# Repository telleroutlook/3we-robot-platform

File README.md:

<div align="center">

# 3WE Robot Platform

**AI-First Open Infrastructure for Embodied Robotics**

[-orange.svg)](sdk/threewe/)

An open-source robot platform for Embodied AI research — a consistent Python API
across simulation and real hardware, with <$500 reproducible hardware.

> **Status:** Active development. Mock backend is functional. Hardware builds and Gazebo integration are being validated — no completed physical prototype video yet.

> **A note on Sim2Real:** The Python API stays the same when you switch backends, but
> sim-to-real transfer in practice still requires task-specific tuning (sensor models,
> noise, dynamics). We provide presets for common scenarios; we don't claim the gap
> away. See [Sim-to-Real Gap](docs/sim_to_real_gap.md) for what works, what doesn't,
> and where you'll likely need to do downstream work.

*Autonomous navigation in office_v2 scene — 360° LiDAR, real-time obstacle avoidance, 4 lines of Python*

</div>

> **Note:** The animation above is a concept demo (generated with matplotlib), not a Gazebo simulation or real hardware recording. It illustrates the target API and navigation behavior.

### Try it now — 30 seconds, zero dependencies beyond numpy

<div align="center">

</div>

```bash
git clone https://github.com/telleroutlook/3we-robot-platform.git
cd 3we-robot-platform && pip install -e sdk/threewe/
python examples/navigate_office.py
```

> The recording was made with [`demo/record_demo.sh`](demo/record_demo.sh) — clone the repo and run it yourself to verify.

---

## 5 Lines to a Moving Robot

```python
from threewe import Robot

async with Robot(backend="mock") as robot:
    image = robot.get_image()
    await robot.move_to(x=2.0, y=1.0)
    pose = robot.get_pose()
```

Switch `backend="mock"` to `backend="gazebo"` or `backend="real"` — the Python API stays the same. Sensor models and sim configs may still need task-specific tuning; see [Sim-to-Real Gap](docs/sim_to_real_gap.md).

---

## Why 3we?

| If you are... | 3we gives you... | Start here |
|:---|:---|:---|
| **AI/ML Researcher** | Gymnasium envs, VLM/VLA integration, trajectory recording — focus on your model, not ROS2 | [Getting Started (AI)](docs/getting_started_ai.md) |
| **Robotics Student** | Full stack from PCB to Python, <$500 hardware, production-grade code instead of toy examples | [Getting Started (Basic)](docs/getting_started_basic.md) |
| **RL Practitioner** | `gymnasium.make("3we/Navigation-v1")` — standard RL interface with sim-to-real presets for common tasks | [Getting Started (AI)](docs/getting_started_ai.md) |
| **Hardware Builder** | Open BOM, assembly guide, CERN-OHL-P licensed PCB + structure | [Assembly Guide](docs/assembly_guide.md) |

---

## Quick Start

> **Status:** The `threewe` SDK is under active development. `pip install threewe` is not yet available on PyPI. Install from source to try it today:

```bash
git clone https://github.com/telleroutlook/3we-robot-platform.git
cd 3we-robot-platform
pip install -e sdk/threewe/
```

```python
import asyncio
from threewe import Robot

async def main():
    # "mock" backend works immediately — no ROS2 or Gazebo required
    async with Robot(backend="mock") as robot:
        # Navigate
        result = await robot.move_to(x=2.0, y=1.0)
        print(f"Reached: {result.success}")

        # VLM-powered instruction (requires: pip install threewe[ai])
        result = await robot.execute_instruction("go to the red door")

        # Get sensor data
        scan = robot.get_lidar_scan()
        imu = robot.get_imu()

asyncio.run(main())
```

> **Backends**: Use `backend="mock"` to try the API instantly, `"gazebo"` for physics simulation (requires ROS2), `"isaac_sim"` for GPU-accelerated parallel simulation, or `"real"` for physical hardware.

<details>
<summary><b>Actual output (from the recording above)</b></summary>

```console
$ pip install -e sdk/threewe/
Successfully installed threewe-0.1.0a0

$ python examples/navigate_office.py
============================================================
  3we Robot Platform — Office Navigation Demo
============================================================

[3we] Robot initialized  backend=mock  scene=office_v2

  Start pose: (1.0, 1.0)
  LiDAR: 360 rays, nearest obstacle: 0.99m

  Following path: 5 waypoints

[3we] Navigating to (2.0, 3.0)...
[3we] Planning path... distance=2.2m
[3we]   pos=(1.5, 2.1)  heading=63°  remaining=1.0m
[3we] Goal reached  distance=2.2m  time=4.5s
[3we] Navigating to (7.0, 3.5)...
[3we] Planning path... distance=5.0m
[3we]   pos=(4.0, 3.2)  heading=6°  remaining=3.0m
[3we] Goal reached  distance=5.0m  time=10.0s
...

  Final pose: (12.0, 10.0)
  Total distance: 20.5m
  Result: success

============================================================
```

</details>

### RL Training

```python
import gymnasium
import threewe.gym  # registers environments

env = gymnasium.make("3we/Navigation-v1")
obs, info = env.reset()

for _ in range(1000):
    action = env.action_space.sample()
    obs, reward, terminated, truncated, info = env.step(action)
    if terminated or truncated:
        obs, info = env.reset()
```

### Benchmarks

```bash
threewe benchmark run --task pointnav --episodes 100 --backend gazebo
```

See the [Benchmark Leaderboard](docs/leaderboard.md) for baseline results and submission instructions.

---

## Capabilities

| Capability | Status | Details |
|------------|--------|---------|
| Consistent Python API across backends | ✅ Ready | 4 backends (mock/gazebo/isaac_sim/real), same Robot class — task-specific sim tuning still required ([details](docs/sim_to_real_gap.md)) |
| Imitation Learning Data | ✅ Ready | `save_lerobot()` export + HuggingFace Hub push/pull |
| VLM/LLM Control | ✅ Ready | GPT-4o / Qwen-VL, async API decoupled from 50Hz control loop |
| Hardware Safety | ✅ Ready | 3-tier watchdog: 500ms cmd_vel timeout, 1s software WDT, 1.6s hardware WDT (TPS3813) |
| RL Gymnasium Envs | ✅ Ready | 4 standard envs (PointNav, Exploration, ObjectNav, VLN) + multi-agent |
| Edge AI Inference | ✅ Ready | Hailo-8L M.2 accelerator (13 TOPS) on Raspberry Pi 5 |
| VLA Model Deploy | ✅ Ready | ONNX / PyTorch / Hailo HEF, `from_pretrained()` from Hub |
| Domain Randomization | ✅ Ready | Physics, visual, and sensor noise — configurable per-episode |
| RGB-D Depth Camera | ✅ Ready | `get_rgbd_image()` API, native depth in Isaac Sim |
| Modular Install | ✅ Ready | `threewe` / `threewe[sim]` / `threewe[ai]` / `threewe[all]` |

---

## Architecture

```mermaid
flowchart TB
    A["<b>Your Python Code</b><br/>robot.move_to() · robot.get_image() · robot.execute_instruction()"]
    B["<b>threewe Python API</b><br/>Robot · Types · Config · AI (VLM/VLA) · Gym · Data · Benchmark"]
    C1["<b>MockBackend</b><br/>Zero-dep 2D<br/>kinematic sim"]
    C2["<b>GazeboBackend</b><br/>Gazebo Harmonic<br/>+ ros_gz_bridge"]
    C3["<b>RealBackend</b><br/>ROS2 Topics"]
    C4["<b>IsaacSimBackend</b><br/>GPU-accelerated<br/>parallel RL"]
    D["<b>ROS2 Jazzy + Nav2</b><br/>/cmd_vel · /scan · /odom · /camera · NavigateToPose Action"]
    E["<b>Firmware (ESP32-S3)</b><br/>Motor PID · Encoders · IMU · Safety Relay · micro-ROS"]
    F["<b>Hardware Layer</b><br/>Mecanum · DRV8833 · HC-SR04/LD06 · BNO055 · Battery · E-Stop"]

    A --> B
    B --> C1 & C2 & C3 & C4
    C1 & C2 & C3 & C4 --> D
    D --> E
    E --> F
```

---

## Platform Comparison

> Different tools for different needs. This table highlights where 3we fits — it is not a claim of superiority.

| Feature | **3we** | TurtleBot 4 | LeRobot | Isaac Lab |
|:--------|:---:|:---:|:---:|:---:|
| Python API (no ROS2 knowledge needed) | Yes | No | N/A | Partial |
| Same API, mock → sim → real | Yes | No | No | Yes |
| Open Hardware (PCB + BOM) | Full | Partial | N/A | N/A |
| Gymnasium Interface | Yes | No | Partial | Yes |
| VLM/VLA Integration | Yes | No | Yes | No |
| Hardware Cost | <$500 | ~$1200 | ~$2000+ | N/A |
| Payload Hot-plug Bus | PBC-34 | USB | N/A | N/A |
| Safety (HW E-stop) | Yes | Software | N/A | N/A |
| Community / Maturity | Early stage | Established | Active | Active |

---

## Hardware Specs

| Spec | Standard v2 |
|:-----|:---|
| Drive | 4-wheel Mecanum (65mm), omnidirectional |
| MCU | ESP32-S3 (dual-core 240MHz) |
| SBC | Raspberry Pi 5 (8GB) |
| AI Accelerator | Hailo-8L (13 TOPS) |
| LiDAR | LD06 (360°, 12m range) |
| IMU | BNO055 (9-axis fused) |
| Max Velocity | 0.5 m/s linear, 1.0 rad/s angular |
| Battery | 7.4V Li-ion, ~2h runtime |
| Safety | ISO 13850-inspired hardware E-stop + dual-channel relay (not certified) |
| Connectivity | Wi-Fi + BLE (+ 4G/5G optional) |
| Reproduction Cost | <$500 |

---

## Repository Structure

```
3we-robot-platform/
├── sdk/threewe/          # AI-First Python package (pip install threewe)
│   ├── src/threewe/      #   Robot, Types, Backends, Gym, AI, Data, Benchmark
│   └── tests/            #   309 unit tests
├── examples/             # Ready-to-run demo scripts
├── firmware/             # ESP32-S3 firmware (ESP-IDF + micro-ROS)
├── ros2_ws/              # ROS2 packages (Nav2, SLAM, Gazebo, Perception)
├── hardware/             # Open hardware (KiCad PCB, BOM, mechanical)
├── sdk/payload_interface/# Payload communication library
├── sdk/web_control/      # TypeScript Web Components control panel
├── monitoring/           # Prometheus + Grafana observability
└── docs/                 # Guides, API reference, tutorials
```

---

## Installation Options

> **Current**: Install from source with `pip install -e sdk/threewe/`. The commands below will work once the package is published to PyPI.

```bash
# Core (types, Robot class, config)
pip install threewe

# With simulation (adds gymnasium)
pip install threewe[sim]

# With AI integration (adds openai, Pillow)
pip install threewe[ai]

# With data recording (adds h5py)
pip install threewe[data]

# Everything
pip install threewe[all]
```

For the **real hardware** backend, you also need ROS2 Jazzy:
```bash
# Ubuntu 24.04
sudo apt install ros-jazzy-desktop
```

---

## Examples

| Script | Description | Backend |
|:-------|:-----------|:--------|
| [`navigate_office.py`](examples/navigate_office.py) | Multi-waypoint navigation with verbose output | mock |
| [`hello_world.py`](examples/hello_world.py) | Connect, capture image, navigate | mock |
| [`rl_obstacle_avoidance.py`](examples/rl_obstacle_avoidance.py) | PPO training in simulation | mock |
| [`slam_exploration.py`](examples/slam_exploration.py) | Autonomous SLAM exploration | mock |
| [`data_collection.py`](examples/data_collection.py) | Record trajectories for imitation learning | mock |
| [`vlm_navigation.py`](examples/vlm_navigation.py) | GPT-4o visual navigation | mock + API key |
| [`sim2real_demo.py`](examples/sim2real_demo.py) | Same code, different backends | gazebo |

### Jupyter Notebooks

Step-by-step tutorials in [`notebooks/`](notebooks/). Most require ROS2 + Gazebo unless noted:

| Notebook | Topic | Requires |
|:---------|:------|:---------|
| [01_hello_world](notebooks/01_hello_world.ipynb) | Connect, sensors, basic navigation | Gazebo |
| [02_slam_exploration](notebooks/02_slam_exploration.ipynb) | Autonomous mapping | Gazebo |
| [03_point_navigation](notebooks/03_point_navigation.ipynb) | Waypoints and path following | Gazebo |
| [04_rl_training](notebooks/04_rl_training.ipynb) | Gymnasium + PPO training | mock (works standalone) |
| [05_data_collection](notebooks/05_data_collection.ipynb) | Record trajectories, export to LeRobot | Gazebo |

---

## Roadmap

- [x] **Phase 1**: ESP32 firmware + ROS2 stack + Hardware design
- [x] **Phase 1**: `threewe` Python API + Mock backend
- [x] **Phase 1**: Gymnasium environments + VLM/VLA integration
- [x] **Phase 1**: Benchmark framework + Example scripts
- [ ] **Phase 1**: Gazebo/Isaac Sim backends (interface done, integration testing in progress)
- [ ] **Phase 1**: PyPI publishing (`pip install threewe`)
- [x] **Phase 2**: On-robot status display panel (1.3" OLED SH1106, 3-key navigation, 5 pages, fault codes)
- [ ] **Phase 2**: Hardware Abstraction Layer for 3rd-party robots
- [ ] **Phase 2**: Foundation model fine-tuning pipelines
- [ ] **Phase 3**: 3we Hub (model/dataset sharing)
- [ ] **Phase 3**: Multi-robot fleet management

---

## Blog & Dev Notes

Engineering deep-dives at [3we.org/blog](https://3we.org/blog/overview/):

| Post | Topic |
|:-----|:------|
| [Dev Log #1: Why These Parts](https://3we.org/blog/dev-log-001/) | ESP32-S3 vs STM32, mecanum wheels, PBC-34 bus design, honest project status |
| [Sim2Real: Same Code to Real Hardware](https://3we.org/blog/sim2real-practice/) | Backend abstraction, domain randomization, validation protocol |
| [Build a $300 ROS2 Research Robot](https://3we.org/blog/build-robot/) | Complete BOM, assembly, software setup |
| [30 Lines: Let GPT-4o Control a Robot](https://3we.org/blog/vlm-control/) | VLM perception-action loop, local model support |

---

## Licensing

| Component | License | File |
|:----------|:--------|:-----|
| Firmware & Software | Apache License 2.0 | [`LICENSE`](LICENSE) |
| Hardware Designs | CERN-OHL-P v2 | [`LICENSE-HARDWARE`](LICENSE-HARDWARE) |
| Documentation | CC BY-SA 4.0 | [`LICENSE-DOCS`](LICENSE-DOCS) |

### Attribution

Commercial use is welcome and free of charge. The licenses require that derivative
works include attribution to this project. Recommended format:

> This product is based on the open-source [3we Robot Platform](https://github.com/telleroutlook/3we-robot-platform).

For academic citations, see [`CITATION.cff`](CITATION.cff).

---

## Contributing

We welcome contributions! See **[CONTRIBUTING.md](CONTRIBUTING.md)** for development setup, branch strategy, and PR process.

---

## Safety Notice

> [!WARNING]
> This platform contains **moving mechanical parts** and **lithium batteries**.

- Safety relay design is **inspired by** ISO 13850 but is **not certified** — do not use for safety-critical applications without independent certification
- Always verify E-stop function before operation
- Never bypass or modify the safety relay circuit
- Follow battery handling guidelines in documentation

---

<div align="center">

Copyright 2025-2026 [telleroutlook](https://github.com/telleroutlook) · [3we-robot-platform](https://github.com/telleroutlook/3we-robot-platform)

</div>

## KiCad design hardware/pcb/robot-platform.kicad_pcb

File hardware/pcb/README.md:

# PCB Design Documentation

## Overview

The robot-platform mainboard integrates the ESP32-S3 MCU, motor drivers, power management, sensor interfaces, and the PBC-34 payload connector on a single 4-layer PCB.

## Board Specifications

| Parameter | Value |
|-----------|-------|
| Dimensions | 120 × 90 mm |
| Layers | 4 (Signal - GND - Power - Signal) |
| Minimum trace width | 0.15 mm |
| Minimum via | 0.3 mm drill / 0.6 mm pad |
| Clearance | 0.2 mm |
| Copper weight | 1 oz (outer), 1 oz (inner) |
| Surface finish | ENIG (lead-free) |
| Board thickness | 1.6 mm |

## Layer Stack

| Layer | Usage |
|-------|-------|
| Top | Signal traces, component pads |
| Inner 1 | Ground plane (unbroken) |
| Inner 2 | Power distribution (VBAT, 5V, 3.3V, 12V) |
| Bottom | Signal traces, component pads |

## Power Architecture

```
Battery Pack(s) ─── XT30 ──→ Q8 P-MOS ──→ VBAT Bus (7.4V)
                              (reverse      │
                              protection)   │
                    ┌──────────────────────────┼──────────────────────┐
                    │                          │                      │
                    ▼                          ▼                      ▼
              MP2359 Buck              MP1584EN Buck            [Safety Relay]
              5V / 1.2A                5V / 5A                       │
              (ESP32, sensors)              │                    Coil supply:
                    │               ┌──────┼──────┐           +5V_ESP → SW1b NC
                    ▼               │      │      │           → +5V_ESTOP_COIL
              AP2112K-3.3        Q6a/Q6b   Q3                 → RLY1 coil
              3.3V / 600mA       P-MOS SW  P-MOS SW                  │
              (logic, I2C)          │         │                      ▼
                                    ▼         ▼               Motor DRV8833
                              +5V_PI_SW   +5V_PAYLOAD         (7.4V / 10A max)
                              (Pi5, 3A)   (Payload, 2A)
                              GPIO45 ctrl  MCP23017 ctrl
```

### Supervisory Circuits

- **TPS3813 (U10)**: External watchdog, 1.6s timeout. GPIO46 toggles WDI; if firmware
  hangs, RST pulls ESP32 EN low → hardware reset. Independent of software watchdog.
- **Pi5 Power Switch (Q6a/Q6b/Q7)**: Dual Si2301CDS P-MOS (parallel, 5A total) with
  AO3400A N-MOS driver. GPIO45 HIGH = Pi5 ON. Default OFF at boot (R34 pull-down).
  Standard/Industrial SKU only (DNP on Basic).
- **E-stop Safety Path (SW1b → RLY1)**: The E-stop button has dual NC contact pairs.
  NC2 (SW1b) is in series with the safety relay coil +5V supply. Pressing E-stop
  physically breaks the coil circuit → relay de-energizes → motor power cut. This is
  a pure hardware interlock — zero firmware dependency, compliant with ISO 13850.
  R17 (Q5 gate pull-up) also connects to +5V_ESTOP_COIL so the N-MOS driver loses
  gate drive simultaneously.

## PBC-34 Payload Bus Connector

2×17 pin header (2.54mm pitch), keyed with polarization notch.

| Pin | Function | Rating | Notes |
|-----|----------|--------|-------|
| 1-2 | +5V Power | 3A max | P-MOS soft-start, switched from +5V_PI (MP1584EN 5A rail) via MCP23017 GPA0 |
| 3-4 | +12V Power | 3A max | MOSFET soft-start |
| 5-6 | GND (Power) | — | Wide traces (1mm) |
| 7 | I2C SDA | 3.3V | Direct (shared bus with IMU, INA219, MCP23017) |
| 8 | I2C SCL | 3.3V | Direct (shared bus with IMU, INA219, MCP23017) |
| 9 | UART TX | 3.3V | From payload to platform |
| 10 | UART RX | 3.3V | From platform to payload |
| 11-18 | GPIO ×8 | 3.3V | Via MCP23017 expander |
| 19 | USB D+ | — | Hub downstream port |
| 20 | USB D- | — | Hub downstream port |
| 21 | CAN-H | — | Industrial SKU only |
| 22 | CAN-L | — | Industrial SKU only |
| 23-24 | VBAT Direct | 10A | PPTC protected |
| 25 | ENABLE | Active low | Power control |
| 26 | FAULT | Open drain | Payload fault |
| 27 | DETECT | Mechanical | Spring contact |
| 28 | INT | Active low | Interrupt request |
| 29 | +3.3V Ref | 100mA | Logic reference |
| 30 | ID SCL | — | EEPROM discovery |
| 31 | ID SDA | — | EEPROM discovery |
| 32-34 | GND (Signal) | — | Signal return |

## ESD Protection

- TVS diodes on all external-facing pins (PBC-34, USB, motor connectors)
- ESD rating: IEC 61000-4-2, ±8kV contact / ±15kV air
- Specific parts: PESD5V0S1BB (single-line) on signal pins

## Design Rules

- Power traces: 2mm minimum for motor current paths
- Keep analog (ADC, encoder) traces away from PWM/motor traces
- Ground plane stitching vias every 5mm along board edges
- Motor driver thermal pads connected to internal ground plane
- Decoupling capacitors placed within 3mm of IC power pins
- USB differential pairs: 90Ω impedance controlled
- BNO055 IMU: 100nF + 10µF bulk cap on VDD (C4 + C17, per datasheet)

## MCP23017 Interrupt (TP1)

INTA is active-low open-drain with 10k pull-up (R36), routed to test pad TP1.
Mirror mode combines both ports onto INTA. Current firmware uses 100ms polling.

To enable interrupt-driven operation (future rev or user modification):
1. Bridge TP1 to an available ESP32 GPIO via bodge wire
2. Configure GPIO as input with pull-up, falling-edge interrupt
3. In ISR: read MCP23017 INTCAP register to identify source (payload detect,
   DRV8833 fault, GPIO change)
4. Reduces I2C bus load from continuous polling to event-driven

## Status Display Panel (Optional Add-on)

1.3" SH1106 128×64 OLED with 3 integrated tactile buttons (UP/DOWN/OK).
Connects via existing I2C bus (address 0x3C) + MCP23017 button inputs.

| Signal | Connection | Notes |
|--------|-----------|-------|
| OLED VCC | +3V3 | From I2C header |
| OLED GND | GND | From I2C header |
| OLED SDA | I2C_SDA (GPIO 1) | Shared bus |
| OLED SCL | I2C_SCL (GPIO 2) | Shared bus |
| BTN_UP | MCP23017 GPB6 | Active-low with internal pull-up |
| BTN_DOWN | MCP23017 GPB7 | Active-low with internal pull-up |
| BTN_OK | MCP23017 GPA4 | Active-low with internal pull-up |

No PCB modification required. Module mounts on chassis top panel via M2 standoffs,
connects through 4-pin GH1.25 (I2C) + 3-pin GH1.25 (buttons) to mainboard headers.

I2C bus load: +10pF capacitance (SH1106 typical). Existing 2.2kΩ pull-ups remain
adequate for 400kHz with total bus capacitance < 250pF.

## Industrial SKU Motor Driver Strategy

The mainboard PCB uses DRV8833 (dual H-bridge, 1.2A/ch) for Basic and Standard SKUs. The Industrial SKU requires BTS7960 (43A half-bridge) for 550 motors at 12V.

### Approach A: External Module (Initial Batch)

#### CAN Bus Termination (R9, 120Ω)

R9 is a 120Ω CAN bus termination resistor, **shipped as DNP (Do Not Populate)** on
Basic and Standard SKUs (which have no CAN bus).

**For Industrial SKU:** R9 MUST be populated (soldered) when:
- The robot is at one end of the CAN bus (most single-robot setups)
- The Payload device does NOT provide its own termination

**Do NOT populate R9 when:**
- The robot sits in the middle of a multi-node CAN chain
- Both ends of the bus are already terminated by other nodes

CAN bus requires exactly two 120Ω terminations — one at each physical end of the
bus. Measure 60Ω between CAN-H and CAN-L (bus powered off) to confirm correct
termination.

Recommended for first production run (< 100 units):

- Mainboard PCB unchanged — no BTS7960 footprint on-board
- Motor power output via 4× XT30 connectors (2-pin, 30A rated)
- PWM/EN signals routed to GH1.25-4P connector (PWM_H, PWM_L, VCC, GND)
- Off-the-shelf BTS7960 module (¥18/ea, 2 modules for 4 motors)
- Mounting: M3 standoffs on chassis plate, 100mm motor wires

Advantages: No PCB re-spin, fast iteration, replaceable if damaged.

### Approach B: Integrated PCB (Volume Production)

For production run > 500 units:

- New KiCad variant: `robot-platform-industrial.kicad_pcb`
- Replace DRV8833 area with 4× BTS7960 half-bridge ICs
- Add ACS712-05B current sense on each motor phase
- Requires: larger board (140×100mm), heatsink mounting holes, thermal vias under driver pads
- Internal ground plane extended for thermal relief
- Estimated NRE: ¥3,000 (4-layer prototype + stencil)

### Decision Criteria

| Factor | Approach A | Approach B |
|--------|-----------|-----------|
| Unit cost (motor driver) | ¥36 (2 modules) | ¥24 (bare ICs + passives) |
| PCB NRE | ¥0 | ¥3,000 |
| Break-even | — | ~250 units |
| Assembly complexity | Higher (wiring) | Lower (SMT) |
| Reliability | Module connectors | Soldered joints |
| Thermal management | Module heatsink | PCB thermal vias + external heatsink |

**Current decision**: Approach A for initial batch (Q2 2026). Evaluate Approach B after 100-unit production feedback.

## Manufacturing Notes

- Gerber format: RS-274X
- Drill file: Excellon format
- Pick and place: centroid + rotation per component
- All resistors/capacitors 0402 minimum (0603 preferred for hand assembly)
- QFN packages require solder paste stencil (0.12mm thickness)

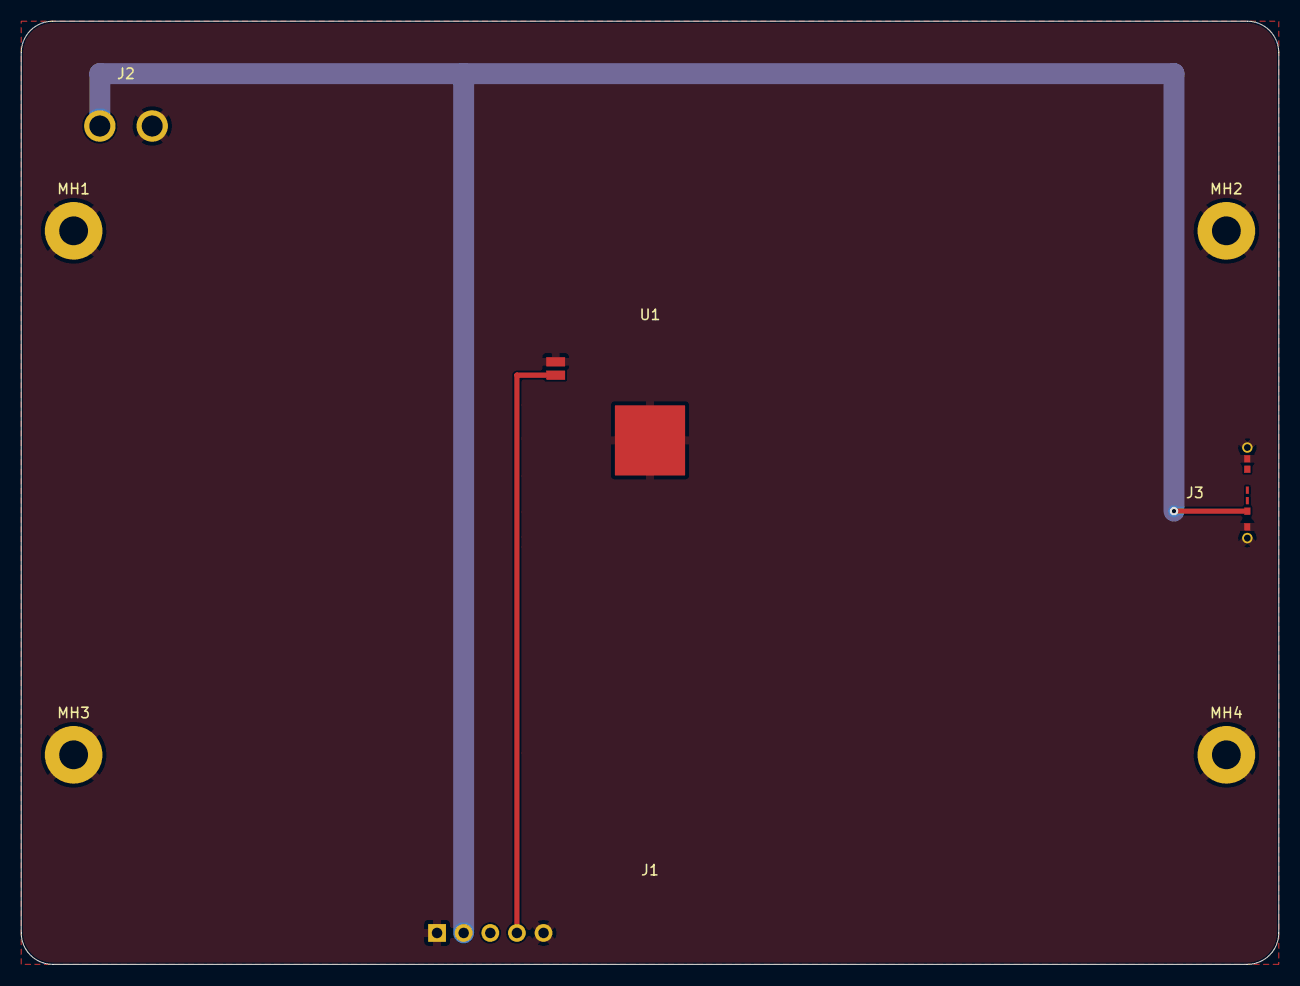
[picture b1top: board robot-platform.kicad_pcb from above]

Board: 4 copper layers, 120.0 x 90.0 mm, 8 parts (0 on the bottom side), 3 nets.

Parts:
J1: PBC-34_Payload_Bus; PBC-34
J2: XT30_Battery; XT30_Male_Vertical
J3: USB_C; USB_C_Receptacle_HRO_TYPE-C-31-M-12
MH1, MH2, MH3, MH4: MountingHole_M2.5; MountingHole_2.7mm_M2.5_Pad_Via
U1: ESP32-S3-WROOM-1

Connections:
+3V3: J1.4, U1.2
GND: J1.1, J1.5, J2.2, J3.A1, J3.A12, J3.S1, J3.S2, MH1.1, MH2.1, MH3.1, MH4.1, U1.1, U1.GND
VBAT: J1.2, J2.1, J3.A9

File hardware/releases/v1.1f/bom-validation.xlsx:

序号 | 型号 | 封装 | 参数/规格 | 单套用量 | 品牌 | 分类 | 商品编号 | 物料编码 | 位号
1 | TYPE-C-31-M-12 | 贴板SMD | USB-C 16P 母座 双排贴片 卧式 USB 2.0 | 2 | HRO Parts | 连接器 | C165948 |  | J3
2 | XT30PW-M | PCB直插 | XT30 公头 30A 大电流 PCB 焊接 垂直 | 2 | AMASS | 电源连接器 | C2913321 |  | J2
3 | 排针 2.54mm 1x40P 单排直针 | 2.54mm 直插 | 排针 单排 直针 40Pin 镀金 (掰断到34Pin) | 2 | BOOMELE | 排针排母 | C124378 |  | J1
4 | ESP32-S3-WROOM-1-N16R8 | SMD-28 | WiFi+蓝牙模块 16MB Flash 8MB PSRAM | 1 | 乐鑫(Espressif) | 无线模块 | C2913203 |  | U1
5 | M2.5*8 盘头机牙螺丝 | 机械 | 十字盘头 M2.5x8mm 304不锈钢 | 10 | AOFENG | 螺丝 | C3008063 |  | MH1-MH4
6 | M2.5 六角螺母 | 机械 | DIN934 M2.5 六角螺母 304不锈钢 | 10 | AOFENG | 螺母 | C3008145 |  | MH1-MH4

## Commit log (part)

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2026-05-08 chore: initialize open-source robot-platform repository
    - README.md with project overview, architecture, quick start guide
    - Triple license: Apache 2.0 (code), CERN-OHL-P v2 (hardware), CC BY-SA 4.0 (docs)
    - CLAUDE.md with development guidelines and safety rules
    - CONTRIBUTING.md with branch strategy, commit format, DCO
    - NOTICE file with third-party dependency attributions
    - GitHub issue templates (bug report, feature request)
2026-05-08 fix(security): resolve 18 critical/high issues from code review
    Firmware security (CRITICAL):
    - motor_control: add safety_is_estopped() guard to motor_set_speed/mecanum_drive
    - main: load DTLS PSK from NVS, refuse to start with unprovisioned key
    - main: call ota_signing_init() with NVS-stored public key
    - udp_transport: gate command dispatch behind CONFIG_ROBOT_ALLOW_PLAINTEXT_CTRL
    - dtls_transport: enforce DTLS 1.2 minimum version floor
2026-05-08 feat(firmware): enhance safety module and DTLS transport with test mocks
    - Extend safety.c with additional safety state handling
    - Add DTLS transport improvements
    - Expand test mocks for mbedTLS and ESP-IDF stubs
    - Add mbedtls/ssl_cache.h mock header
2026-05-09 docs: add robot platform hero image to README
2026-05-09 fix(ci): add shell: bash for container jobs and fix managed_components
    - Add shell: bash to all container job steps that use 'source' command
    (ros:humble default shell is sh which lacks 'source' builtin)
    - Make managed_components EXTRA_COMPONENT_DIRS conditional in
    CMakeLists.txt (directory only exists after component manager runs)
2026-05-09 fix(firmware): add custom partition table with 2MB app partitions
    Binary size with DTLS/PSK features exceeds default 1MB app partition.
    Custom 8MB flash partition layout with 2x 2MB OTA partitions, coredump,
    and NVS encryption key storage.
    Also adds fail-fast: false to firmware-build matrix so all SKU variants
    report their results independently.
2026-05-10 fix(ci): resolve integration test and Docker build failures
    - Integration test: publish battery messages repeatedly with spin_once
    to ensure the diagnostics node receives data before asserting
    - Docker: fix nginx permission denied errors when running as non-root
    by granting ownership of /var/log/nginx, /var/lib/nginx, /run to
    the robot user, and disabling the 'user' directive in nginx.conf
2026-05-10 refactor(hardware): consolidate 4 SKUs to 3 (Basic/Standard/Industrial)
    - Remove Pro SKU, absorb into enlarged Standard
    - Standard chassis: 300×250mm → 400×320mm with 65mm mecanum wheels
    - Standard payload capacity: 2kg → 5kg (supports robot arm payloads)
    - Standard mounting: M4 120×100mm pattern (compatible with SO-101 base)
    - Add weight distribution guidelines for front-mounted payloads
    - Rename bom_pro.csv → bom_optional_addons.csv
2026-05-10 fix: resolve 22 cross-layer issues from full codebase review
    Critical (5):
    - firmware/motor_control: eliminate spinlock gap between PWM write and stopped flag
    - firmware/dtls_transport: add ssl_mutex for mbedtls_ssl_write in handle_session_io
    - firmware/ota_update: re-read flash after write to verify SHA-256 matches signed hash
    - firmware/safety: consolidate relay monitoring into single critical section, add volatile
    - firmware/captive_portal: force DNS answer count to 1, prevent attacker-controlled reflection
2026-05-11 feat(firmware): add dual-channel safety relay feedback monitoring
    Add SAFETY_RELAY_FB2 (GPIO 22) for dual-channel redundant relay
    monitoring required by CE PL d Category 3. Both feedback channels
    must agree — a mismatch triggers immediate E-stop and escalates to
    SAFETY_RELAY_FAULT after 3 occurrences. Self-test validates both
    channels at boot.
    NOTE: KiCad schematic must be updated to match — replace RLY1 single
2026-05-11 fix(firmware): add adc_manager.c to SRCS list
    adc_manager.c provides adc_manager_init() and adc_manager_get_handle()
    used by battery.c and main.c. The file was created during the shared ADC
    manager refactoring but was not added to the CMakeLists.txt SRCS list,
    causing linker errors (undefined reference) in all SKU builds.
2026-05-11 fix(sim): switch sensor render engine from ogre2 to ogre
    ogre2 (OGRE-Next) fails to initialize in CI containers with Mesa
    software rendering, causing Gazebo Fortress to crash on startup.
    ogre (OGRE 1.x) has full software rendering support via Mesa/EGL.
    Sensor accuracy is identical — only visual fidelity differs, which
    is irrelevant for physics simulation and automated testing.
2026-05-11 docs: fix documentation inconsistencies with code and cross-document alignment
    - Fix OTA signing algorithm: Ed25519 → ECDSA P-256 (matches firmware implementation)
    - Fix web_control framework: Lit → vanilla TypeScript Web Components (no Lit dependency)
    - Fix component count: 7 → 8 Web Components (system-status was missing from count)
    - Fix ROS2 package count: 4 → 8 packages (add robot_competition, robot_diagnostics,
    robot_docking, robot_perception)
    - Fix firmware test count: 23 → 26 unit test files
2026-05-12 feat(firmware,hardware): align dock detection spec + add 12V P-MOS switch with extensible power rail abstraction
    Issue 1 — Dock detection method alignment:
    - Update hardware spec: Pin 1 is dual-purpose (charge sense + ADC dock
    detection), Pin 4 marked RESERVED for future use
    - Add Kconfig option CONFIG_ROBOT_DOCKING_DIGITAL_DETECT for optional
    secondary digital GPIO detection (OR-logic with analog)
    - Extend charging_detect module with charge_detect_method_t enum and
2026-05-12 feat(scripts): add cross-layer validation for params, pins, BOM, and Kconfig
    - validate-robot-params.ts: firmware chassis geometry ↔ ROS2 launch file per SKU
    - validate-pin-conflicts.py: GPIO pin conflict detection with #ifdef-aware SKU scoping
    - validate-bom-firmware.py: BOM I2C addresses and motor specs ↔ firmware defines
    - validate-kconfig-constraints.py: SKU mutual exclusion and feature-gating rules
    - Makefile: add individual targets + expand 'validate' to run all 5 validators
    - CI: add firmware constraint checks to full-validation.yml
2026-05-13 feat(sdk): add MockBackend for zero-dependency usage + sim2real report enhancement
    Phase 1: MockBackend (backends/mock.py)
    - Kinematic simulation with box-room (20m x 15m)
    - Requires only numpy — no ROS2, no Gazebo
    - Full BackendBase interface: perception, action, navigation
    - Deterministic output for testability
    - 24 dedicated tests (all passing)
2026-05-13 chore(dev): add /opt/homebrew/bin to PATH in Claude Code settings
    Ensures python3.12 (installed via Homebrew) is found by the
    pre-commit validation hook across all sessions.
2026-05-14 fix(security): resolve remaining Semgrep blocking findings
    - Add nosemgrep to remaining strncpy calls (captive_portal, wifi_provision)
    - Move nosemgrep comment to first line of torch.load multiline call
    - Change ws:// placeholder to wss:// in web_basic and web_control HTML
    - Add nosemgrep to xml.etree.ElementTree imports in test files
    - Add nosemgrep to urlopen call in ota_manager_node
    - Exclude firmware certs directory and test/ directories from Semgrep scan
2026-05-15 docs: embed asciinema recording in README
2026-05-16 hw(pcb): add reverse polarity protection Q8, MP1584EN feedback divider R37/R38
    Fix 17: AO3401A P-MOS (Q8) between XT30 and VBAT bus. Gate=GND: ON when
    correct polarity (Vgs=-7.4V), OFF when reversed. Rds=55mΩ, drop=0.165V@3A.
    Fixes README 'P-MOS OR' claim that had no corresponding circuit.
    Fix 18: MP1584EN (U5) feedback network added — R37=52.3k/R38=10k sets
    Vout = 0.8×(1+52.3/10) = 4.98V. Previously missing (bare IC requires
    external FB divider). PI_FB net connects midpoint to U5 pin 5.
2026-05-16 fix(firmware): add compile-time guard for ENCODER_CPR == 0 (#70)
2026-05-16 fix(firmware): move heartbeat_feed() from DTLS to micro-ROS transport
    DTLS is the remote operator channel (laptop/phone over WiFi), not the
    Pi 5 communication path. Feeding the heartbeat from DTLS meant a remote
    client could keep the Pi 5 watchdog alive even when the Pi 5 was dead.
    Move heartbeat_feed() to cmd_vel_callback in microros_transport.c,
    which only fires when the Pi 5 is actively sending commands via UART.
2026-05-16 fix(firmware): return last voltage on ADC read failure in battery
    When adc_manager_read() fails (mutex timeout), return the existing
    voltage_avg instead of injecting raw=0 into the moving average.
    Without this, transient ADC failures could drag voltage_avg toward
    0V, falsely triggering BATT_CRITICAL and an unwarranted E-stop.
    Issue #106
2026-05-16 fix(firmware): add rate limiting to remote OTA path
    Extract exponential backoff logic into shared ota_rate_limit_check()
    used by both local upload handler and perform_ota_from_url. Previously
    the remote URL path had no rate limiting, allowing repeated flash write
    abuse via DTLS command channel. Both paths now share s_fail_streak and
    cooldown state. (#126)
2026-05-16 docs: add copyright notices and project attribution
    - NOTICE: add project copyright header (Apache 2.0 §4(d) compliance)
    - README: add copyright footer with GitHub profile link
    - PCB: add '3we-robot-platform' text on B.Silkscreen layer
    - main.c, __init__.py: add Copyright line to SPDX headers
2026-05-16 docs: update commercial contact email to teller.lin@outlook.com
2026-05-17 feat(ros2): add operation timeouts to collection manager
    Add configurable timeouts for PICKING (15s), RETURNING (60s), DUMPING
    (10s), and overall operation (300s). Prevents indefinite oscillation
    when ball detection is flaky or Nav2 goals hang. Replaces hardcoded 3s
    dump time with dump_timeout_s parameter.
2026-05-17 fix(ci): add rclpy.qos mock and upgrade pip in ros:humble containers
    - robot_docking tests: add missing rclpy.qos mock to
    test_docking_degraded_mode.py (broke when E-stop QoS was added)
    - integration-tests.yml / full-validation.yml: upgrade pip before
    installing threewe SDK to fix hatchling needing packaging>=24.0
    (packaging.licenses) in the ros:humble container
2026-05-17 feat(docs): add MkDocs site, leaderboard JSON, and CI deployment
    - Add mkdocs.yml with Material theme and mkdocstrings for Python SDK
    - Create docs/index.md landing page and docs/reference/api.md for auto-generated API
    - Create data/leaderboard.json as single source of truth for benchmark results
    - Add .github/workflows/docs.yml for Cloudflare Pages deployment
    - Add docs-serve and docs-build targets to Makefile
    - Fix broken cross-repo relative links in docs (use GitHub URLs)
2026-05-19 chore(ci): bump actions/github-script from 7.1.0 to 9.0.0 (#14)
    Bumps [actions/github-script](https://github.com/actions/github-script) from 7.1.0 to 9.0.0.
    - [Release notes](https://github.com/actions/github-script/releases)
    - [Commits](https://github.com/actions/github-script/compare/f28e40c7f34bde8b3046d885e986cb6290c5673b...3a2844b7e9c422d3c10d287c895573f7108da1b3)
    ---
    updated-dependencies:
    - dependency-name: actions/github-script

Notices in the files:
hardware/pcb/robot-platform.kicad_pcb:
SPDX-License-Identifier: CERN-OHL-P-2.0
parts and their libraries:
LICENSE: CERN-OHL-P-2.0
